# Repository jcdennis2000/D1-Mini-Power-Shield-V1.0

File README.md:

# D1-Mini-Power-Shield-V1.0

The D1 Mini is a great little Arduino compatable board with built in WiFi that means it can be placed almost anywhere! The only problem is that powering the device from far away can be hard, as the D1 Mini only takes 5V or 3.3V. 
Never fear! You can now use the D1 Mini Power Shield to supply 9-12V to your D1 Mini! It has a voltage regulator, two capacitors, a power LED, and supplies a regulated 5V current directly into the 5V pin on the D1 Mini

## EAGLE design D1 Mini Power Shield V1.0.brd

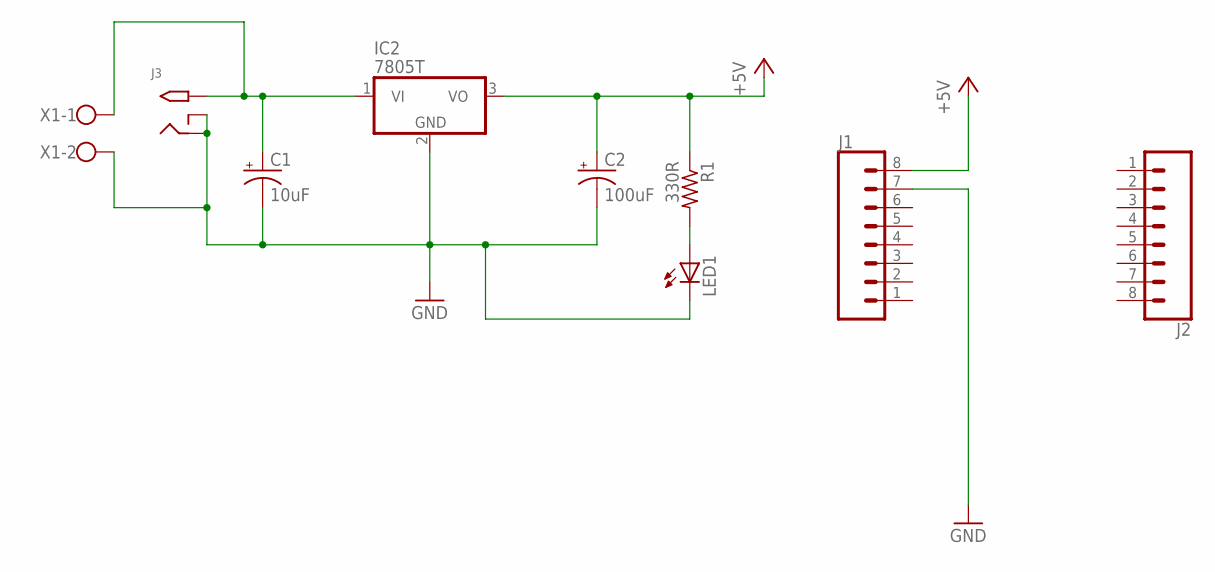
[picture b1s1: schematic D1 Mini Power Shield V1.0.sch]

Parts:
C1: 10uF; E2,5-7
C2: 100uF; E2,5-7
IC2: 7805T; TO220H
J1, J2: CONN_08"; 1X08
J3: 2.1MMJACKTHM; PJ-102A
LED1: LED3MM
R1: 330R; 0207/2V
X1: W237-102

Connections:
+5V: C2.+, IC2.3 (VO), J1.8, R1.1
GND: C1.-, C2.-, IC2.2 (GND), J1.7, J3.RING, J3.RING_SW, LED1.K (C), X1.2
unnamed: C1.+, IC2.1 (VI), J3.TIP, X1.1
unnamed: LED1.A, R1.2

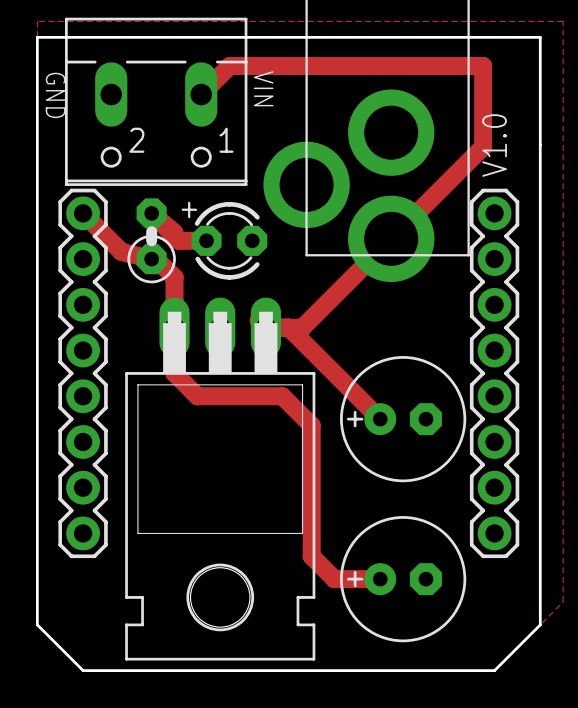
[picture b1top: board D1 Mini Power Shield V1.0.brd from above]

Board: 2 copper layers, 27.9 x 35.2 mm, 9 parts (0 on the bottom side), 4 nets.

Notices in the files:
D1 Mini Power Shield V1.0.brd:
Dennistries (c) 2019
parts and their libraries:
SparkFun-Connectors: Licensing: Creative Commons ShareAlike 4.0 International - https://creativecommons.org/licenses/by-sa/4.0
